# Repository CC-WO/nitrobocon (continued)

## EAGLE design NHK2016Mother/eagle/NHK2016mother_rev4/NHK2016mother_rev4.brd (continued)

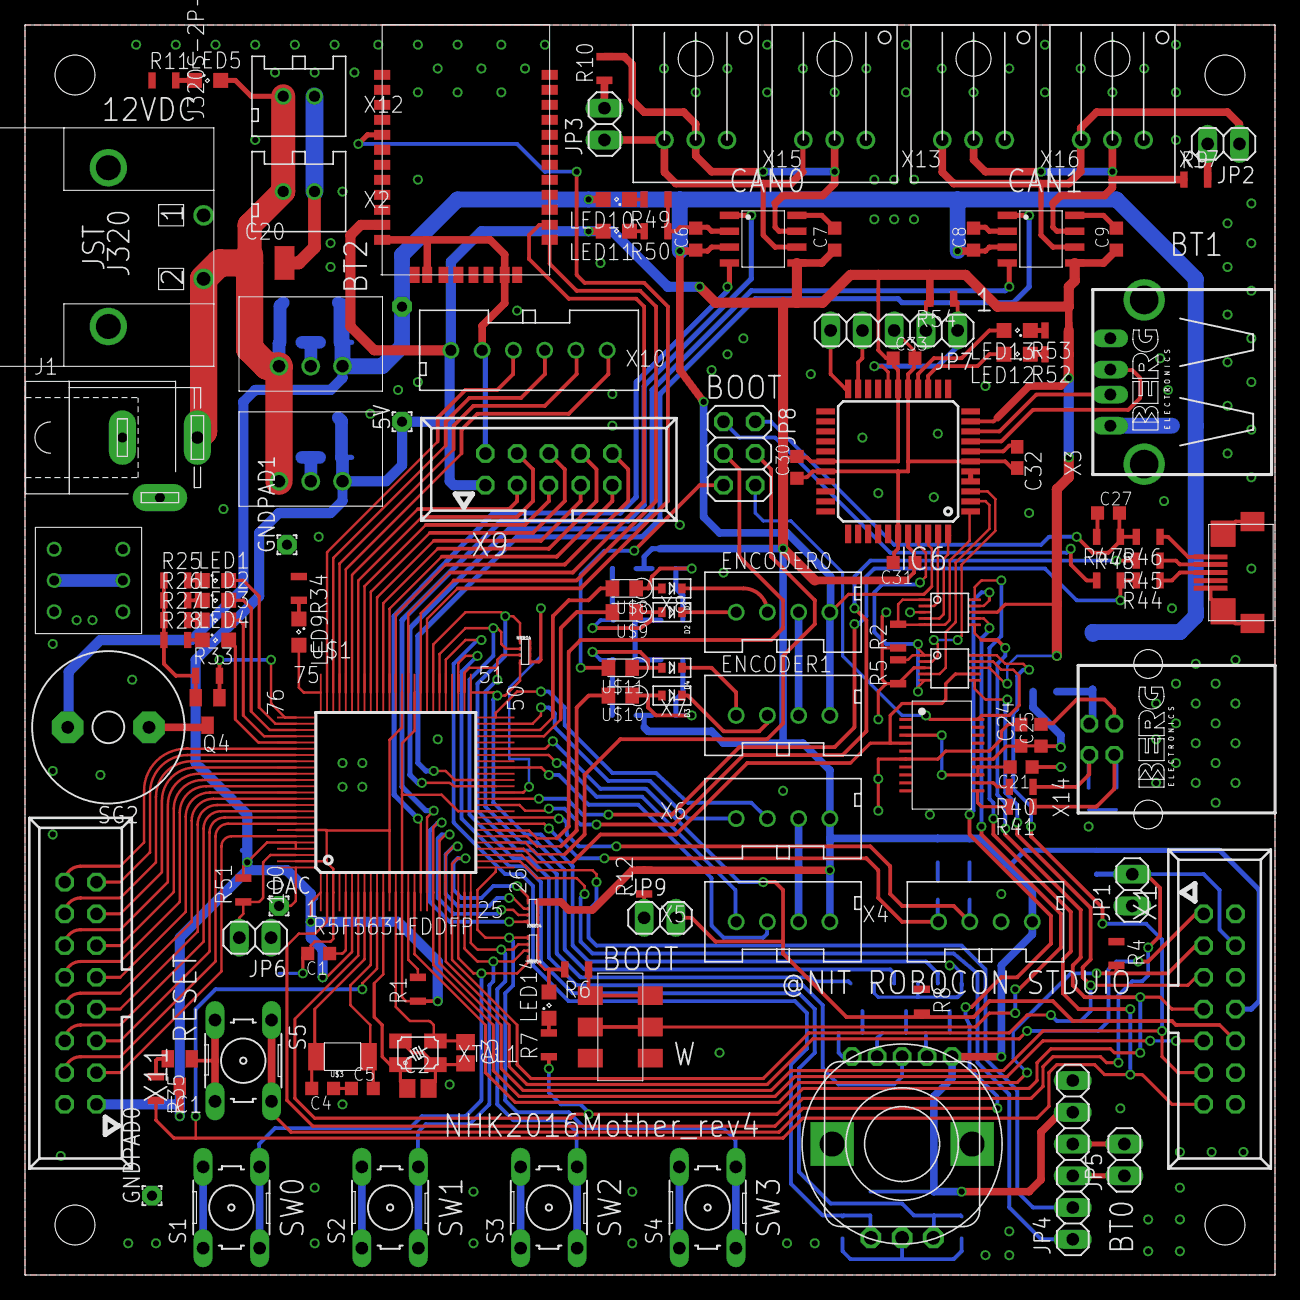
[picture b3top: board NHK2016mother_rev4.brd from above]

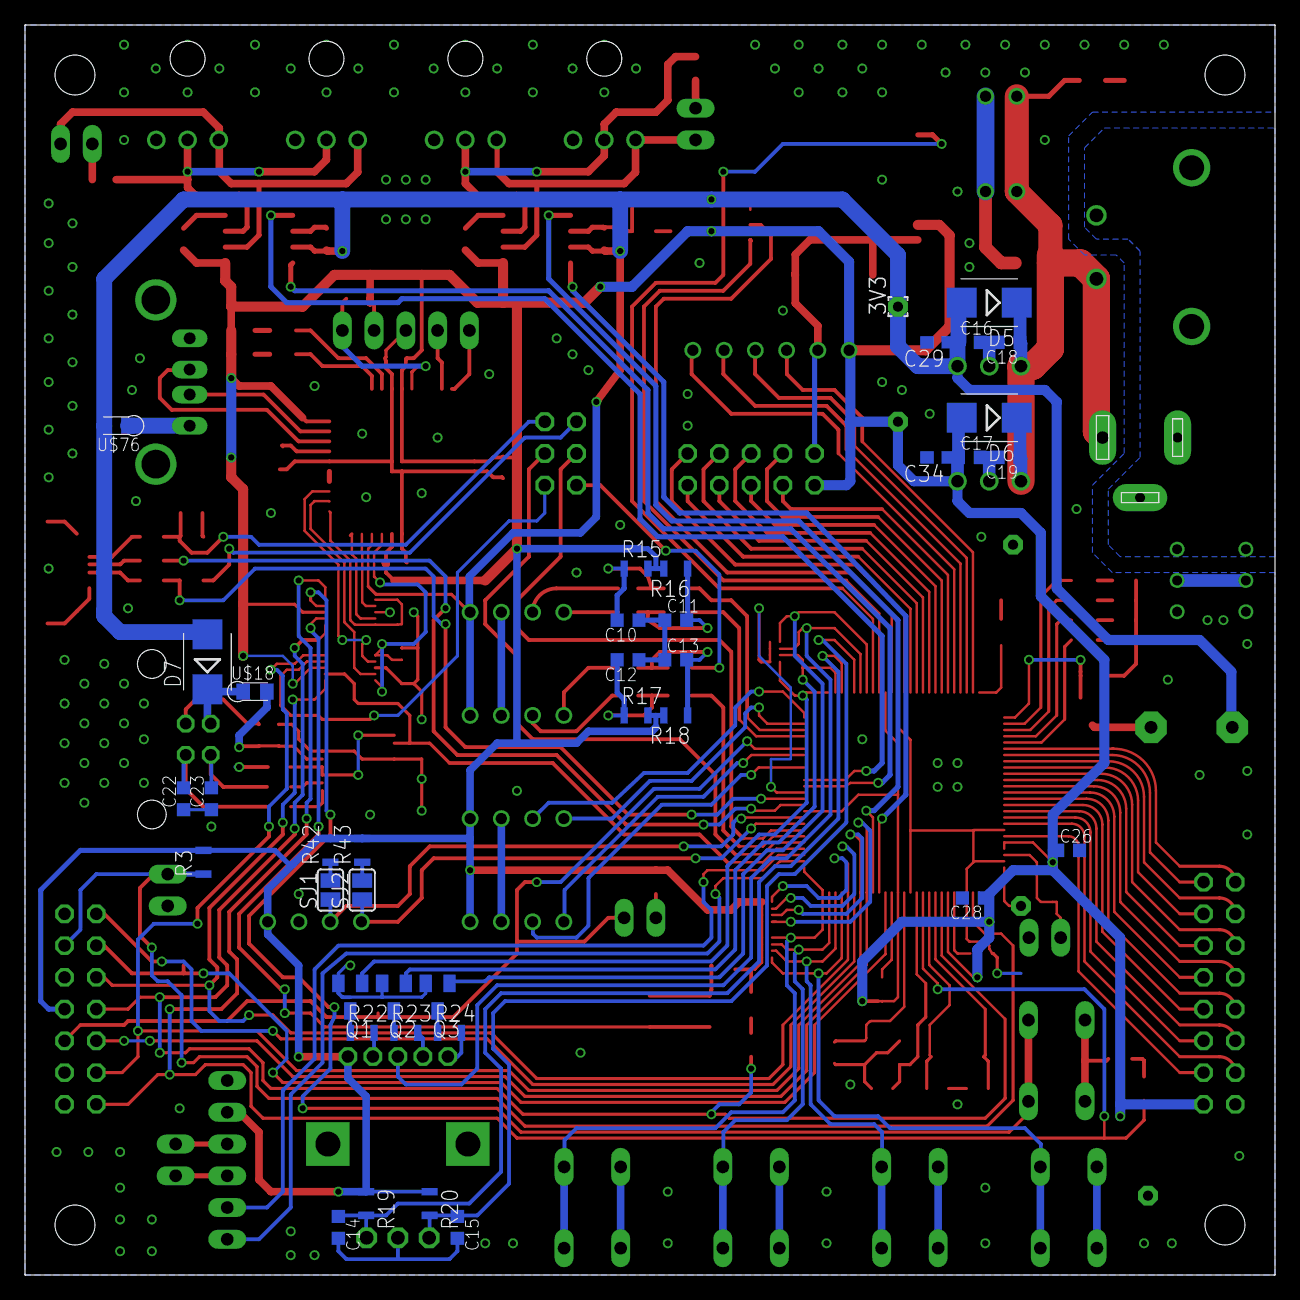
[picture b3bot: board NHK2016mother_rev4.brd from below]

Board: 2 copper layers, 100.0 x 100.0 mm, 166 parts (39 on the bottom side), 159 nets.

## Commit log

2020-09-27 add SurfaceRX and NHK2016mother
2020-09-27 Mod README.md
